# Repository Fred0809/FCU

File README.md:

# FCU
Flight controller unit for up to 6 motors

The board takes 5V from power delivery board mounted below using JST connector alone with battey current and voltage measurements.

Six JST connectors on sides are used to connect to ESCs on each motor. It will use CAN to comunicate between modules.

60.8 x 57.6 mm

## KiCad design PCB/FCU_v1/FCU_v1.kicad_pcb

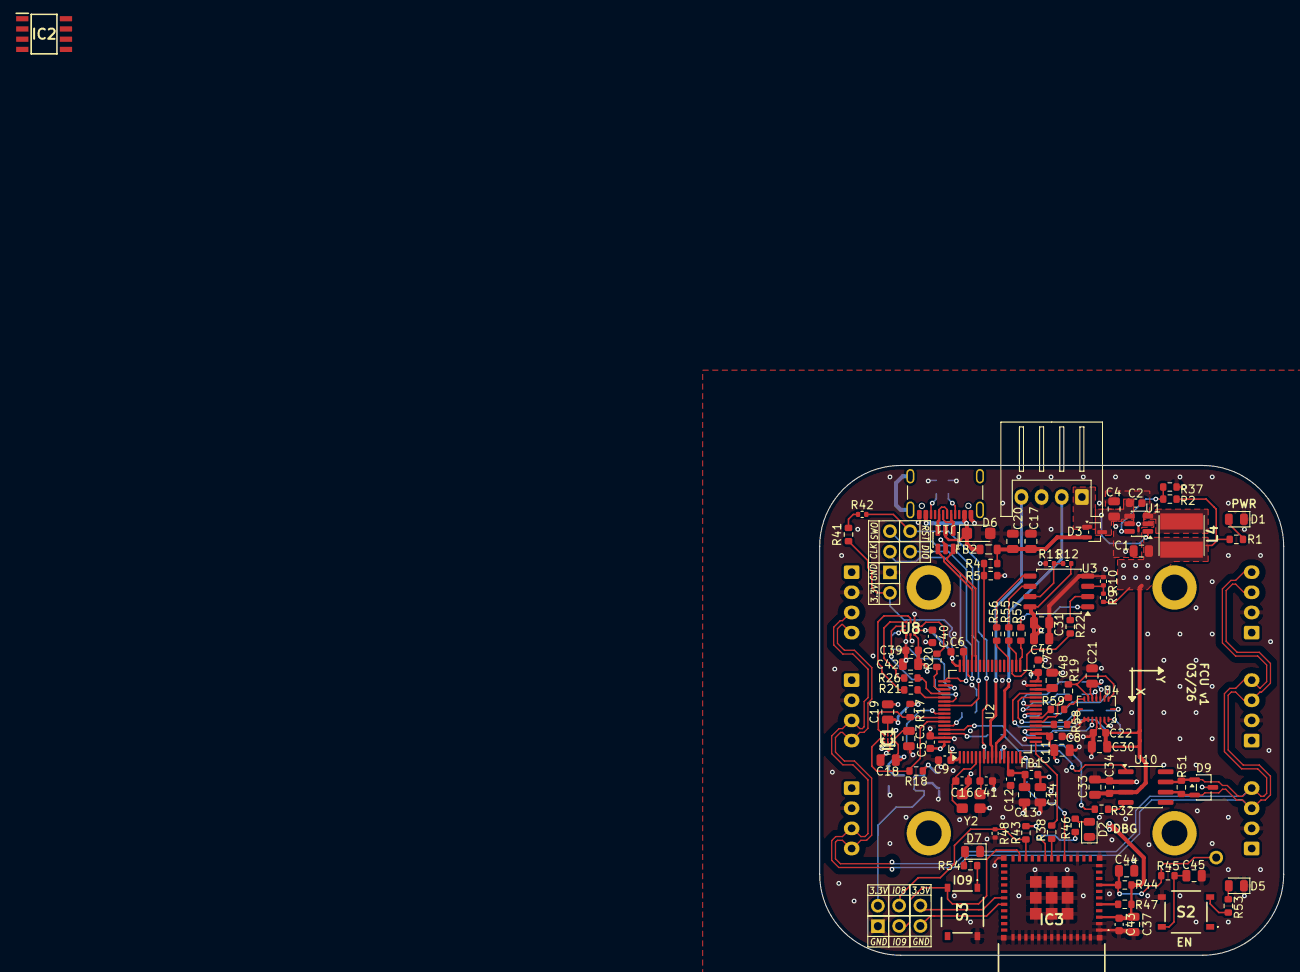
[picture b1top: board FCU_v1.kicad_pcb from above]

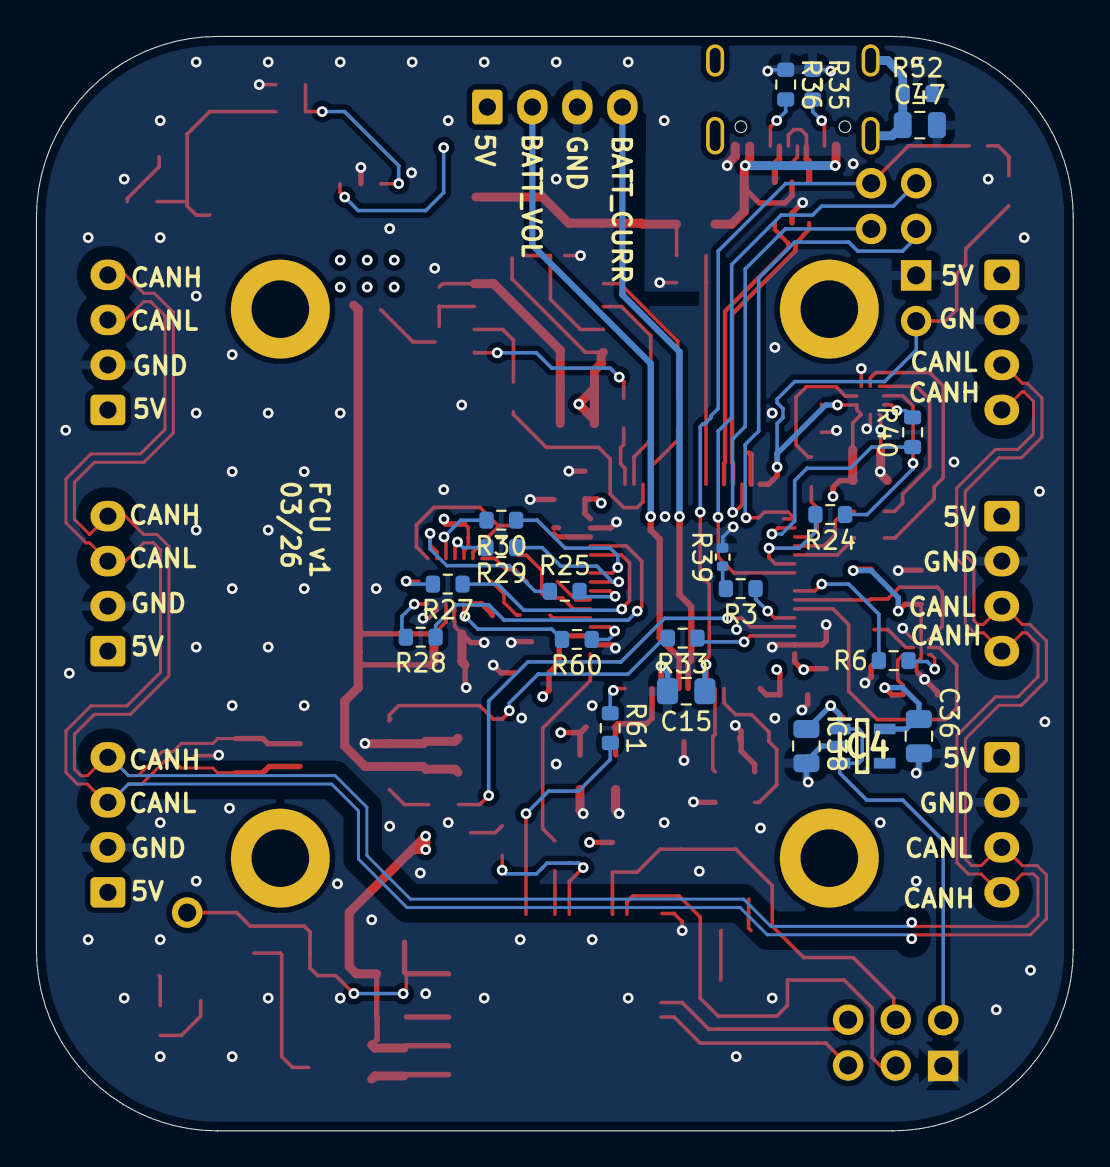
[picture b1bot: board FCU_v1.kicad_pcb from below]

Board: 4 copper layers, 57.6 x 60.8 mm, 131 parts (21 on the bottom side), 97 nets.

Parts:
C1: 22u/6.3V; C_0805_2012Metric
C2: 100n/10V; C_0603_1608Metric
C3: 2u2/6.3V; C_0805_2012Metric
C4: 10u/10V; C_0805_2012Metric
C5, C6, C7, C8, C9, C22, C39, C40, C43: 100n; C_0603_1608Metric
C11, C37, C46: 10u; C_0805_2012Metric
C12: 10n; C_0603_1608Metric
C13, C14, C38, C44: 1u; C_0805_2012Metric
C15: 100n; C_0805_2012Metric_Pad1.18x1.45mm_HandSolder
C16, C41: 6p8; C_0603_1608Metric
C17: 22u/10V; C_0805_2012Metric
C18, C19, C21, C31, C45: 100n; C_0805_2012Metric
C20: 100n/10V; C_0805_2012Metric
C30, C36, C42: 2u2; C_0805_2012Metric
C33: 1uF; C_0805_2012Metric
C34: 100nF; C_0603_1608Metric
C47: 22u; C_0805_2012Metric
C48: 4u7; C_0805_2012Metric
D1, D2, D5, D7: LED; LED_0805_2012Metric
D3: BAT54CWFILMY; SOT-323_SC-70
D6: SMF54A; D_SMF
D9: ESD2CAN24DBZRQ1; SOT-23-3
FB1: FCM1608KF-601T03; L_0603_1608Metric
FB2: 120R at 100 MHz; L_0805_2012Metric
H1, H2, H3, H4: MountingHole_Pad; MountingHole_3.2mm_M3_ISO14580_Pad
IC1: BMM350; BGA9C40P3X3_128X128X54
IC2: TCAN3414DR; SOIC127P600X175-8N
IC3: ESP32-C3-MINI-1-N4X; ESP32C3MINI1N4X
IC4: TPS7A2018PDBVR; SOT95P280X145-5N
J1, J5, J6, J7, J8, J9, J10: Conn_01x04_Pin; JST_XH_S4B-XH-A_1x04_P2.50mm_Horizontal
J3, J12, J13, J14, J15, J16: Conn_01x02_Pin; PinHeader_1x02_P2.54mm_Vertical
J11: USB_C_Receptacle_USB2.0_16P; USB_C_Receptacle_GCT_USB4105-xx-A_16P_TopMnt_Horizontal
J17: Conn_01x01_Pin; PinHeader_1x01_P2.54mm_Vertical
L4: 744042001; WE-TPC_4818_482892
R1: 2k; R_0603_1608Metric
R2: 450k; R_0603_1608Metric
R3, R41, R43, R44, R45, R47: 10k; R_0603_1608Metric
R4: 33k; R_0603_1608Metric
R5: 82k; R_0603_1608Metric
R6, R19, R20, R21, R22, R24, R25, R26, R27, R28, R29, R30, R40, R55, R56, R57, R58, R59, R60, R61: 33R; R_0603_1608Metric
R9, R10, R11, R12, R39, R42, R48: DNP; R_0402_1005Metric
R17, R18: 4.7k; R_0603_1608Metric
R32, R33: 22Ω; R_0603_1608Metric
R35, R36, R52: 5k1; R_0603_1608Metric
R37: 100k; R_0603_1608Metric
R38, R46, R53, R54: 4k7; R_0603_1608Metric
R51: 120R; R_0603_1608Metric
S2, S3: PTS526SM15SMTR2_LFS; PTS526SM15SMTR2LFS
U1: TPS62A02APDDCR; SOT-23-6
U2: STM32F412RETx; LQFP-64_10x10mm_P0.5mm
U3: W25Q128JVSIM; SOIC-8_5.3x5.3mm_P1.27mm
U4: BMI088; Bosch_LGA-16_4.5x3mm_P0.5mm_LayoutBorder7x1y_ClockwisePinNu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
U7: USBLC6-2SC6; SOT-23-6
U8: BMP581
U10: SN65HVD232; SOIC-8_3.9x4.9mm_P1.27mm
Y2: 24MHz; Crystal_SMD_3225-4Pin_3.2x2.5mm

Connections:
+3.3VA: C12.1, C13.1, FB1.1, U2.13 (VDDA)
+5V: D3.1, J1.1, J5.1, J6.1, J7.1, J8.1, J9.1, J10.1
+5V_FCU: C2.1, C4.1, D3.3, U1.1 (EN), U1.4 (VIN)
+VBUS: C17.1, C20.1, D3.2, FB2.2, R4.2
/D+: J11.A6 (D+), J11.B6 (D+), U7.6 (I/O1)
/D-: J11.A7 (D-), J11.B7 (D-), U7.4 (I/O2)
/ESP/USART2_RX_ESP: IC3.18 (IO4), R38.1
/IMU/ACCE1_INT: R27.2, U4.16 (INT1)
/IMU/ACCE2_INT: R28.2, U4.1 (INT2)
/IMU/BAR_INT: R40.2, U8.7 (INT)
/IMU/CRST_MAG: C3.1, IC1.C2 (CRST)
/IMU/GYRO1_INT: R29.2, U4.12 (INT3)
/IMU/GYRO2_INT: R30.2, U4.13 (INT4)
/IMU/MAG_INT: IC1.A1 (INT), R6.2
/IMU/SPI1_MISO_ACCE: R19.2, U4.10 (SDO2), U4.15 (SDO1)
/IMU/SPI3_MISO_BAR: R26.1, U8.5 (SDO)
/IMU/VDD_BAR: C18.1, C36.1, IC1.C1 (VDD), IC4.5 (OUT)
/MCU/CAN_TX_STM: R33.1, U2.62 (PB9)
/MCU/CSB_ACCE_STM: R25.2, U2.24 (PC4)
/MCU/CS_BARO_STM: R24.2, U2.54 (PD2)
/MCU/CS_GYRO_STM: R60.1, U2.20 (PA4)
/MCU/CS_MEMO_STM: R57.1, U2.33 (PB12)
/MCU/SPI1_MOSI_STM: R59.1, U2.23 (PA7)
/MCU/SPI1_SCK_STM: R58.1, U2.21 (PA5)
/MCU/SPI2_MOSI_STM: R56.1, U2.36 (PB15)
/MCU/SPI2_SCK_STM: R55.1, U2.34 (PB13)
/MCU/SPI3_MOSI_STM: R21.2, U2.53 (PC12)
/MCU/SPI3_SCK_STM: R20.2, U2.51 (PC10)
/MCU/USART2_TX_STM: R61.1, U2.16 (PA2)
/MCU/VCAP: C48.1, U2.30 (VCAP_1)
/SW_TPS: L4.1, U1.3 (SW)
/USB_VBUS: D6.1 (A1), FB2.1, J11.A4 (VBUS), J11.A9 (VBUS), J11.B4 (VBUS), J11.B9 (VBUS), U7.5 (VBUS)
BAT_CURR: J1.4, U2.9 (PC1)
BAT_VOL: J1.2, U2.10 (PC2)
BOOT: R3.1, U2.60 (BOOT0)
CAN+: D9.1 (K), J5.4, J6.4, J7.4, J8.4, J9.4, J10.4, R51.2, U10.7 (CANH)
CAN-: D9.2 (K), J5.3, J6.3, J7.3, J8.3, J9.3, J10.3, R51.1, U10.6 (CANL)
CAN_RX: R32.1, U2.61 (PB8)
CAN_TX: R33.2, U10.1 (D)
CS_ACCE: R25.1, U4.14 (~CSB1)
CS_BARO: R24.1, U8.6 (CSB)
CS_GYRO: R60.2, U4.5 (~CSB2)
CS_MEMO: R57.2, U3.1 (~CS)
ESP_EN: C44.1, IC3.8 (EN), J17.1, R44.1, R45.2
ESP_GPIO2: IC3.5 (IO2), R47.1
ESP_GPIO8: IC3.22 (IO8), J16.1, R43.1, R48.1
ESP_GPIO9: IC3.23 (IO9), J16.2, S3.3 (NO_1)
GND: C1.2, C2.2, C3.2, C4.2, C5.2, C6.2, C7.2, C8.2, C9.2, C11.2, C12.2, C13.2, C14.2, C15.2, C16.1, C17.2, C18.2, C19.2, C20.2, C21.2, C22.2, C30.2, C31.2, C33.2, C34.2, C36.2, C37.2, C38.2, C39.2, C40.2, C41.1, C42.2, C43.2, C44.2, C45.2, C46.2, C47.2, C48.2, D1.1 (K), D2.1 (K), D5.1 (K), D6.2 (A2), D7.1 (K), D9.3 (A), IC1.B1 (GND), IC1.B2 (ADSEL), IC1.C3 (BYPASS), IC3.1 (GND), IC3.2 (GND_2), IC3.11 (GND_3), IC3.14 (GND_4), IC3.36 (GND_5), IC3.37 (GND_6), IC3.38 (GND_7), IC3.39 (GND_8), IC3.40 (GND_9), IC3.41 (GND_10), IC3.42 (GND_11), IC3.43 (GND_12), IC3.44 (GND_13), IC3.45 (GND_14), IC3.46 (GND_15), IC3.47 (GND_16), IC3.48 (GND_17), IC3.49 (GND_18), IC3.50 (GND_19), IC3.51 (GND_20), IC3.52 (GND_21), IC3.53 (GND_22), IC3.54 (GND_23), IC3.55 (GND_24), IC3.56 (GND_25), IC3.57 (GND_26), IC3.58 (GND_27), IC3.59 (GND_28), IC3.60 (GND_29), IC3.61 (GND_30), IC4.2 (GND), J1.3, J3.2, J5.2, J6.2, J7.2, J8.2, J9.2, J10.2, J11.A1 (GND), J11.A12 (GND), J11.B1 (GND), J11.B12 (GND), J14.2, R5.1, R10.1, R11.1, R35.1, R36.1, R37.2, R39.2, R48.2, R52.2, S2.4 (NO_2), S3.2 (COM_2), U1.2 (GND), U1.5 (PG), U2.12 (VSSA), U2.18 (VSS), U2.31 (VSS), U2.47 (VSS), U2.63 (VSS), U3.4 (GND), U4.2 (GNDA), U4.4 (GNDA), U4.6 (GNDIO), U4.7 (PS), U7.2 (GND), U8.3 (VSS), U8.8 (VSS), U8.9 (VSS), U10.2 (GND), Y2.2, Y2.4
I2C_SCL: IC1.A3 (SCK), R17.2, U2.58 (PB6)
I2C_SDA: IC1.A2 (SDA), R18.2, U2.59 (PB7)
INT_ACCE1: R27.1, U2.28 (PB2)
INT_ACCE2: R28.1, U2.29 (PB10)
INT_BARO: R40.1, U2.50 (PA15)
INT_GYRO1: R29.1, U2.25 (PC5)
INT_GYRO2: R30.1, U2.26 (PB0)
INT_MAG: R6.1, U2.57 (PB5)
NRST: C15.1, J13.1, R42.2, U2.7 (NRST)
unnamed: D1.2 (A), R1.2
unnamed: D2.2 (A), R46.2
unnamed: D5.2 (A), R53.2
unnamed: D7.2 (A), R54.2
unnamed: IC3.19 (IO5), R46.1
unnamed: J11.A5 (CC1), R36.2
unnamed: J11.B5 (CC2), R35.2
unnamed: C47.1, J11.S1 (SHIELD), R52.1
unnamed: R3.2, R39.1
unnamed: R41.2, R42.1
unnamed: C45.1, R45.1, S2.2 (COM_2)
unnamed: R53.1, S2.3 (NO_1)
unnamed: R54.1, S3.1 (COM_1)
unnamed: R2.2, R37.1, U1.6 (FB)
unnamed: R22.2, U3.2 (DO/IO_{1})
unnamed: R11.2, R12.1, U3.7 (~HOLD/~RESET/IO_{3})
unnamed: R9.1, R10.2, U3.3 (~WP/IO_{2})
unnamed: R32.2, U10.4 (R)
OSC_IN: C16.2, U2.5 (PH0), Y2.3
OSC_OUT: C41.2, U2.6 (PH1), Y2.1
SPI1_MISO: R19.1, U2.22 (PA6)
SPI1_MOSI: R59.2, U4.9 (SDI/SDA)
SPI1_SCK: R58.2, U4.8 (SCK/SCL)
SPI2_MISO: R22.1, U2.35 (PB14)
SPI2_MOSI: R56.2, U3.5 (DI/IO_{0})
SPI2_SCK: R55.2, U3.6 (CLK)
SPI3_MISO: R26.2, U2.52 (PC11)
SPI3_MOSI: R21.1, U8.4 (SDI)
SPI3_SCK: R20.1, U8.2 (SCK)
STM_VDD: C1.1, C5.1, C6.1, C7.1, C8.1, C9.1, C11.1, C14.1, C19.1, C21.1, C22.1, C30.1, C31.1, C33.1, C34.1, C37.1, C38.1, C39.1, C40.1, C42.1, C43.1, C46.1, FB1.2, IC1.B3 (VDDIO), IC3.3 (3V3), IC4.1 (IN), IC4.3 (EN), J3.1, J14.1, L4.2, R1.1, R2.1, R9.2, R12.2, R17.1, R18.1, R41.1, R43.2, R44.2, R47.2, U2.1 (VBAT), U2.19 (VDD), U2.32 (VDD), U2.48 (VDD), U2.64 (VDD), U3.8 (VCC), U4.3 (VDD), U4.11 (VDDIO), U8.1 (VDDIO), U8.10 (VDD), U10.3 (VCC)
SWCLK: J12.2, U2.49 (PA14)
SWDIO: J13.2, U2.46 (PA13)
SWO: J12.1, U2.55 (PB3)
UART_RX_ESP_DBG: IC3.30 (RXD0), J15.2
UART_TX_ESP_DBG: IC3.31 (TXD0), J15.1
USART2_RX: R38.2, U2.17 (PA3)
USART2_TX: IC3.16 (IO10), R61.2
USB_D+: U2.45 (PA12), U7.1 (I/O1)
USB_D-: U2.44 (PA11), U7.3 (I/O2)
VBUS_SENS: R4.1, R5.2, U2.42 (PA9)

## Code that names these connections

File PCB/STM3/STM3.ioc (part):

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Mcu.Name=STM32F412R(E-G)Tx
Mcu.Package=LQFP64
Mcu.UserName=STM32F412RETx
PA11.Mode=Device_Only
PA11.Signal=USB_OTG_FS_DM
PA12.Mode=Device_Only
PA12.Signal=USB_OTG_FS_DP
PA13.Mode=Trace_Asynchronous_SW
PA13.Signal=SYS_JTMS-SWDIO
PA14.Mode=Trace_Asynchronous_SW
PA14.Signal=SYS_JTCK-SWCLK
PA15.GPIOParameters=GPIO_Label
PA15.GPIO_Label=INT_BARO
PA15.Signal=GPIO_Input
PA2.Mode=Asynchronous
PA2.Signal=USART2_TX
PA3.Mode=Asynchronous
PA3.Signal=USART2_RX
PA4.GPIOParameters=GPIO_Label
PA4.GPIO_Label=CS_GYRO
PA4.Signal=GPIO_Output
PA5.Mode=Full_Duplex_Master
PA5.Signal=SPI1_SCK
PA6.Mode=Full_Duplex_Master
PA6.Signal=SPI1_MISO
PA7.Mode=Full_Duplex_Master
PA7.Signal=SPI1_MOSI
PA9.Mode=Activate_VBUS
PA9.Signal=USB_OTG_FS_VBUS
PB0.GPIOParameters=GPIO_Label
PB0.GPIO_Label=INT_GYRO2
PB0.Signal=GPIO_Input
PB10.GPIOParameters=GPIO_Label
PB10.GPIO_Label=INT_ACCE2
PB10.Signal=GPIO_Input
PB12.GPIOParameters=GPIO_Label
PB12.GPIO_Label=CS_MEMO
PB12.Signal=GPIO_Output
PB13.Mode=Full_Duplex_Master
PB13.Signal=SPI2_SCK
PB14.Mode=Full_Duplex_Master
PB14.Signal=SPI2_MISO
PB15.Mode=Full_Duplex_Master
PB15.Signal=SPI2_MOSI
PB2.GPIOParameters=GPIO_Label
PB2.GPIO_Label=INT_ACCE1
PB2.Signal=GPIO_Input
PB3.Mode=Trace_Asynchronous_SW
PB3.Signal=SYS_JTDO-SWO
PB5.GPIOParameters=GPIO_Label
PB5.GPIO_Label=INT_MAG
PB5.Signal=GPIO_Input
PB6.Mode=I2C
PB6.Signal=I2C1_SCL
PB7.Mode=I2C
PB7.Signal=I2C1_SDA
PB8.Mode=CAN_Activate
PB8.Signal=CAN1_RX
PB9.Mode=CAN_Activate
PB9.Signal=CAN1_TX
PC1.Signal=ADCx_IN11
PC10.Mode=Full_Duplex_Master
PC10.Signal=SPI3_SCK
PC11.Mode=Full_Duplex_Master
PC11.Signal=SPI3_MISO
PC12.Mode=Full_Duplex_Master
PC12.Signal=SPI3_MOSI
PC2.Signal=ADCx_IN12
PC4.GPIOParameters=GPIO_Label
PC4.GPIO_Label=CS_ACCE
PC4.Signal=GPIO_Output
PC5.GPIOParameters=GPIO_Label
PC5.GPIO_Label=INT_GYRO1
PC5.Signal=GPIO_Input
PD2.GPIOParameters=GPIO_Label
PD2.GPIO_Label=CS_BARO
PD2.Signal=GPIO_Output
PH0\ -\ OSC_IN.Mode=HSE-External-Oscillator
PH0\ -\ OSC_IN.Signal=RCC_OSC_IN
PH1\ -\ OSC_OUT.Mode=HSE-External-Oscillator
PH1\ -\ OSC_OUT.Signal=RCC_OSC_OUT
board=custom

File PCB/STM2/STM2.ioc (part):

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Mcu.Name=STM32G473R(B-C-E)Tx
Mcu.Package=LQFP64
Mcu.UserName=STM32G473RETx
PA0.GPIOParameters=GPIO_Label
PA0.GPIO_Label=INT1_GYRO
PA0.Signal=GPXTI0
PA1.GPIOParameters=GPIO_Label
PA1.GPIO_Label=INT2_ACCEL
PA1.Signal=GPXTI1
PA11.Mode=Device
PA11.Signal=USB_DM
PA12.Mode=Device
PA12.Signal=USB_DP
PA13.Mode=Trace_Asynchronous_SW
PA13.Signal=SYS_JTMS-SWDIO
PA14.Mode=Trace_Asynchronous_SW
PA14.Signal=SYS_JTCK-SWCLK
PA2.GPIOParameters=GPIO_Label
PA2.GPIO_Label=INT1_ACCEL
PA2.Signal=GPXTI2
PA5.Mode=Full_Duplex_Master
PA5.Signal=SPI1_SCK
PA6.Mode=Full_Duplex_Master
PA6.Signal=SPI1_MISO
PA7.Mode=Full_Duplex_Master
PA7.Signal=SPI1_MOSI
PA9.GPIOParameters=GPIO_Label
PA9.GPIO_Label=VBUS_SENS
PA9.Signal=GPIO_Input
PB0.GPIOParameters=GPIO_Label
PB0.GPIO_Label=CSB_MEMO
PB0.Signal=GPIO_Output
PB12.Mode=FDCAN_Activate
PB12.Signal=FDCAN2_RX
PB13.Mode=FDCAN_Activate
PB13.Signal=FDCAN2_TX
PB3.Mode=Trace_Asynchronous_SW
PB3.Signal=SYS_JTDO-SWO
PB5.GPIOParameters=GPIO_Label
PB5.GPIO_Label=GNSS_RST
PB5.Signal=GPIO_Output
PB6.GPIOParameters=GPIO_Label
PB6.GPIO_Label=GNSS_TX
PB6.Mode=Asynchronous
PB6.Signal=USART1_TX
PB7.GPIOParameters=GPIO_Label
PB7.GPIO_Label=GNSS_RX
PB7.Mode=Asynchronous
PB7.Signal=USART1_RX
PB8-BOOT0.GPIOParameters=GPIO_Label
PB8-BOOT0.GPIO_Label=BOOT
PB8-BOOT0.Signal=GPIO_Input
PC0.GPIOParameters=GPIO_Label
PC0.GPIO_Label=BAT_VOL
PC0.Mode=IN6-Single-Ended
PC0.Signal=ADC1_IN6
PC1.GPIOParameters=GPIO_Label
PC1.GPIO_Label=BAT_CURR
PC1.Mode=IN7-Single-Ended
PC1.Signal=ADC2_IN7
PC3.GPIOParameters=GPIO_Label
PC3.GPIO_Label=INT2_GYRO
PC3.Signal=GPXTI3
PC4.GPIOParameters=GPIO_Label
PC4.GPIO_Label=CSB_ACCEL
PC4.Signal=GPIO_Output
PC5.GPIOParameters=GPIO_Label
PC5.GPIO_Label=CSB_GYRO
PC5.Signal=GPIO_Output
PC6.GPIOParameters=GPIO_Label
PC6.GPIO_Label=MAG_INT
PC6.Signal=GPXTI6
PC7.GPIOParameters=GPIO_Label
PC7.GPIO_Label=BAR_INT
PC7.Signal=GPXTI7
PC8.Mode=I2C
PC8.Signal=I2C3_SCL
PC9.Mode=I2C
PC9.Signal=I2C3_SDA
PF0-OSC_IN.Mode=HSE-External-Oscillator
PF0-OSC_IN.Signal=RCC_OSC_IN
PF1-OSC_OUT.Mode=HSE-External-Oscillator
PF1-OSC_OUT.Signal=RCC_OSC_OUT
PG10-NRST.GPIOParameters=GPIO_Label
PG10-NRST.GPIO_Label=NRST
PG10-NRST.Signal=GPIO_Input
RCC.HSE_VALUE=8000000
RCC.SYSCLKFreq_VALUE=16000000
board=custom

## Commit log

2026-01-31 Add FCU v1 schematic PDF
    Added the initial version of the FCU v1 schematic in PDF format to the PCB directory for documentation and reference.
2026-01-31 Add various hardware datasheets in PDF format
    Added multiple datasheet and schematic PDF files for components including MAX-M10M, SparkFun u-blox GNSS, STM32, BMI088, LIS2MDL, LPS22HH, SN65HVD230, STM32G473CB, TLV755P, TPS62133, and W25Q64JV. Th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
2026-01-31 Add accelerometer and barometer schematics
    Added ACCE.kicad_sch for the BMI088 accelerometer/gyroscope and BAROMETER.kicad_sch for the LPS22HH barometer. Also included related KiCad project, schematic, PCB, and backup files for the FCU_v1 boa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
2026-02-02 Remove obsolete sensor schematic files
    Deleted ACCE.kicad_sch, BAROMETER.kicad_sch, MAGNETOMETER.kicad_sch, and related autosave/untitled files from PCB/FCU_v1. Added a backup zip to FCU_v1-backups. This cleans up unused or migrated schem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
2026-02-02 Add FCU block diagram and update PCB layout
    Added FCU.drawio block diagram and new STM/STM2 IOC files. Updated FCU_v1.kicad_pcb with component position changes and connector orientation. Added a new backup ZIP for FCU_v1.
2026-02-02 Update FCU_v1 PCB and add new resistors
    Reworked net assignments and added new nets in FCU_v1.kicad_pcb. Added and repositioned resistors R23 and R28, and updated footprints and net connections. Also updated several backup files and made m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
2026-02-03 Adjust PCB footprint positions and metadata
    Add three FCU_v1 backup archives and apply multiple PCB layout fixes: reposition and reorient many footprints (resistors, capacitors, inductors, diodes, SOT-23, LQFP, LGA, etc.), update pad orientati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
2026-02-04 Added next version v2
    Added notes for next version with what needs to be improved or completely fixed. Notes in schematic file
2026-02-06 Update PCB footprints, positions and backups
    Remove old FCU_v1 backup zips and add new timestamped backups. Apply extensive edits to PCB/FCU_v1.kicad_pcb: reposition and rotate multiple footprints, fix pad orientations, update silkscreen/fab/cr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
2026-02-17 Layout update
2026-02-20 Schematic update
2026-02-20 Repaired library
2026-02-23 Components change and layout update
2026-02-28 Layout cleanup + PCB view
2026-02-28 File name changed
2026-02-28 Readme update
